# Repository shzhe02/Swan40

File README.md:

# Swan40 - A 40-key split keyboard.

My first attempt at designing a custom sleek split keyboard.

Heavily inspired by the [Corne](https://github.com/foostan/crkbd) and [Ferris Sweep](https://github.com/davidphilipbarr/Sweep).

More extensive write-up (in progress): https://shzhe02.com/projects/swan40

The provided ZMK config is essentially:
- 80% [Corne default zmk config and keymap](https://github.com/zmkfirmware/zmk/tree/main/app/boards/shields/corne)
- 10% [Pnohty config for the Ferris Sweep](https://github.com/rayduck/zmk-config)
- 10% Manual configuration for the Swan40

Features:
- Uses the XIAO nRF528420 microcontroller
- Up to 1000 mAh lipo battery without tenting (with 102050 lipo)
- Dual-orientation lipo mounting
- On-off switch hard wired to battery
- Should be compatible with Choc v1 and v2 switches (only v1 tested)
- Hotswap switches
- Plate-mounted switches

BOM:
- 2x XIAO nRF52840 (compatible with both non-sense or sense versions)
- 2x MSK-12C02 switches
- 40x Kailh Low-profile hotswap sockets
- 40x 1N4148W T4 SOD123 diodes
- Some jumper wires (for connecting the battery pads on the PCB to the battery pads on the microcontroller)
- Electrical tape (place over battery-connected pads on PCB after soldering to reduce chances of a short-circuit occuring)
- 40x Kailh Choc v1/v2 switches
- 40x MBK keycaps (or compatible keycaps of your choice)
- (Optional) 2x MBK homing keycaps (In this case, only 38 normal keycaps are needed)

Optional (but recommended) case: https://www.printables.com/model/561315-swan40-case

Case BOM:
- 3x M2 (OD 3.2mm) x 4mm brass inserts
- 3x M2 x 5mm screws (preferrably button head torx (or hex))
- 2x M2 x 10mm screws

Wiring notes:
- Positive and negative battery terminals should be soldered to the BAT+ and BAT- pads on the PCB respectively.
- The BOARD+ and BOARD- pads on the PCB should be soldered to jumper wires connecting them to the BAT+ and BAT- pads on the microcontroller respectively.
- I recommend first connecting the microcontroller to the PCB and using a multimeter to ensure that the switch works and there are no shorts between the BAT+ and BAT- pads of the PCB before connecting the battery.
- When soldering the battery to the PCB, I recommend doing the following:
  - Tape off the end of one of the battery wires with some sort of insulating tape (I used masking tape).
  - Route the taped wire through the battery wire hole on the PCB (check the write up for more details) followed by the other wire.
  - Solder the non-taped wire to its corresponding battery pad on the PCB.
  - After the pad has cooled down, place some insulating tape over the entire pad but leave the other pad exposed.
  - Un-tape the taped wire and solder it to the other battery pad on the PCB.
  - Remove the tape on the other pad, and cover both pads with electrical tape.

~~Potential future improvements:~~
~~- [ ] Make main PCB reversible~~
~~- [ ] Change lipo connection SMD pads to an SMD micro JST 1.25 connector~~
~~- [ ] Figure out a safer (more foolproof) method to connect battery pads of the controller to the PCB.~~
~~- [ ] Design a smaller battery cover for the 500 mAh 602035 lipo~~

No further hardware development will be done. The keyboard works great for me, but I have a few things I dislike about the board (in no particular order):
1. Bluetooth connections are unreliable, both in the pairing process and during operation. While pairing, this keyboard often just refuses to connect to my computer until I clear all profiles, which is quite annoying. During operation, just playing a phone next to the keyboard adds considerable latency.
2. The shift key is placed too low, which means situations where I must hold the key down for a long time or press it many times are uncomfortable.
3. The cables required to connect the battery to the XIAO board. It requires the case to add otherwise unneccessary height below the PCB for clearance, not to mention that it requires insulation around the contacts to protect agasint battery short circuiting.
4. Dust collects on the non-switch parts of the PCBs.

Any future work will be done on brand new keyboard designs that hopefully address these issues.

Credits:
- [foostan's kbd KiCad Library/Symbols/3D Models](https://github.com/foostan/kbd/tree/crkbd4)
    - Located in the directory: pcb/assets/kbd, plate/assets/kbd, left-plate/assets/kbd, and right-plate/assets/kbd
- [Seeed Studio XIAO nRF52840 STEP model - by Maurice Pannard](https://grabcad.com/library/seeed-studio-xiao-nrf52840-sense-1)
    - Located in the directory: pcb/assets/xiao_nrf52840
- [Kailh 1350 Socket (Choc V1 Hotswap sockets) STEP model - by Dennis Lee](https://grabcad.com/library/kailh-1350-socket-2)
    - Located in the directory: pcb/assets/kailh_choc_v1_hotswap
- [MBK Choc Low Profile 1u keycap STEP model - by darryldh](https://www.thingiverse.com/thing:4564253)
    - Located in the directory: pcb/assets/kailh_choc_v1_hotswap
- [MSK-12C02 SMD Slider Switch Footprint - by mzst](https://mzstblog.blogspot.com/2016/01/msk-12c02-smd-slider-switch-spdt-eagle.html)
    - Located in the directory: pcb/assets/MSK-12C02
- Rayduck and Foostan for the ZMK config

Note: Modifications were made to many of the assets.

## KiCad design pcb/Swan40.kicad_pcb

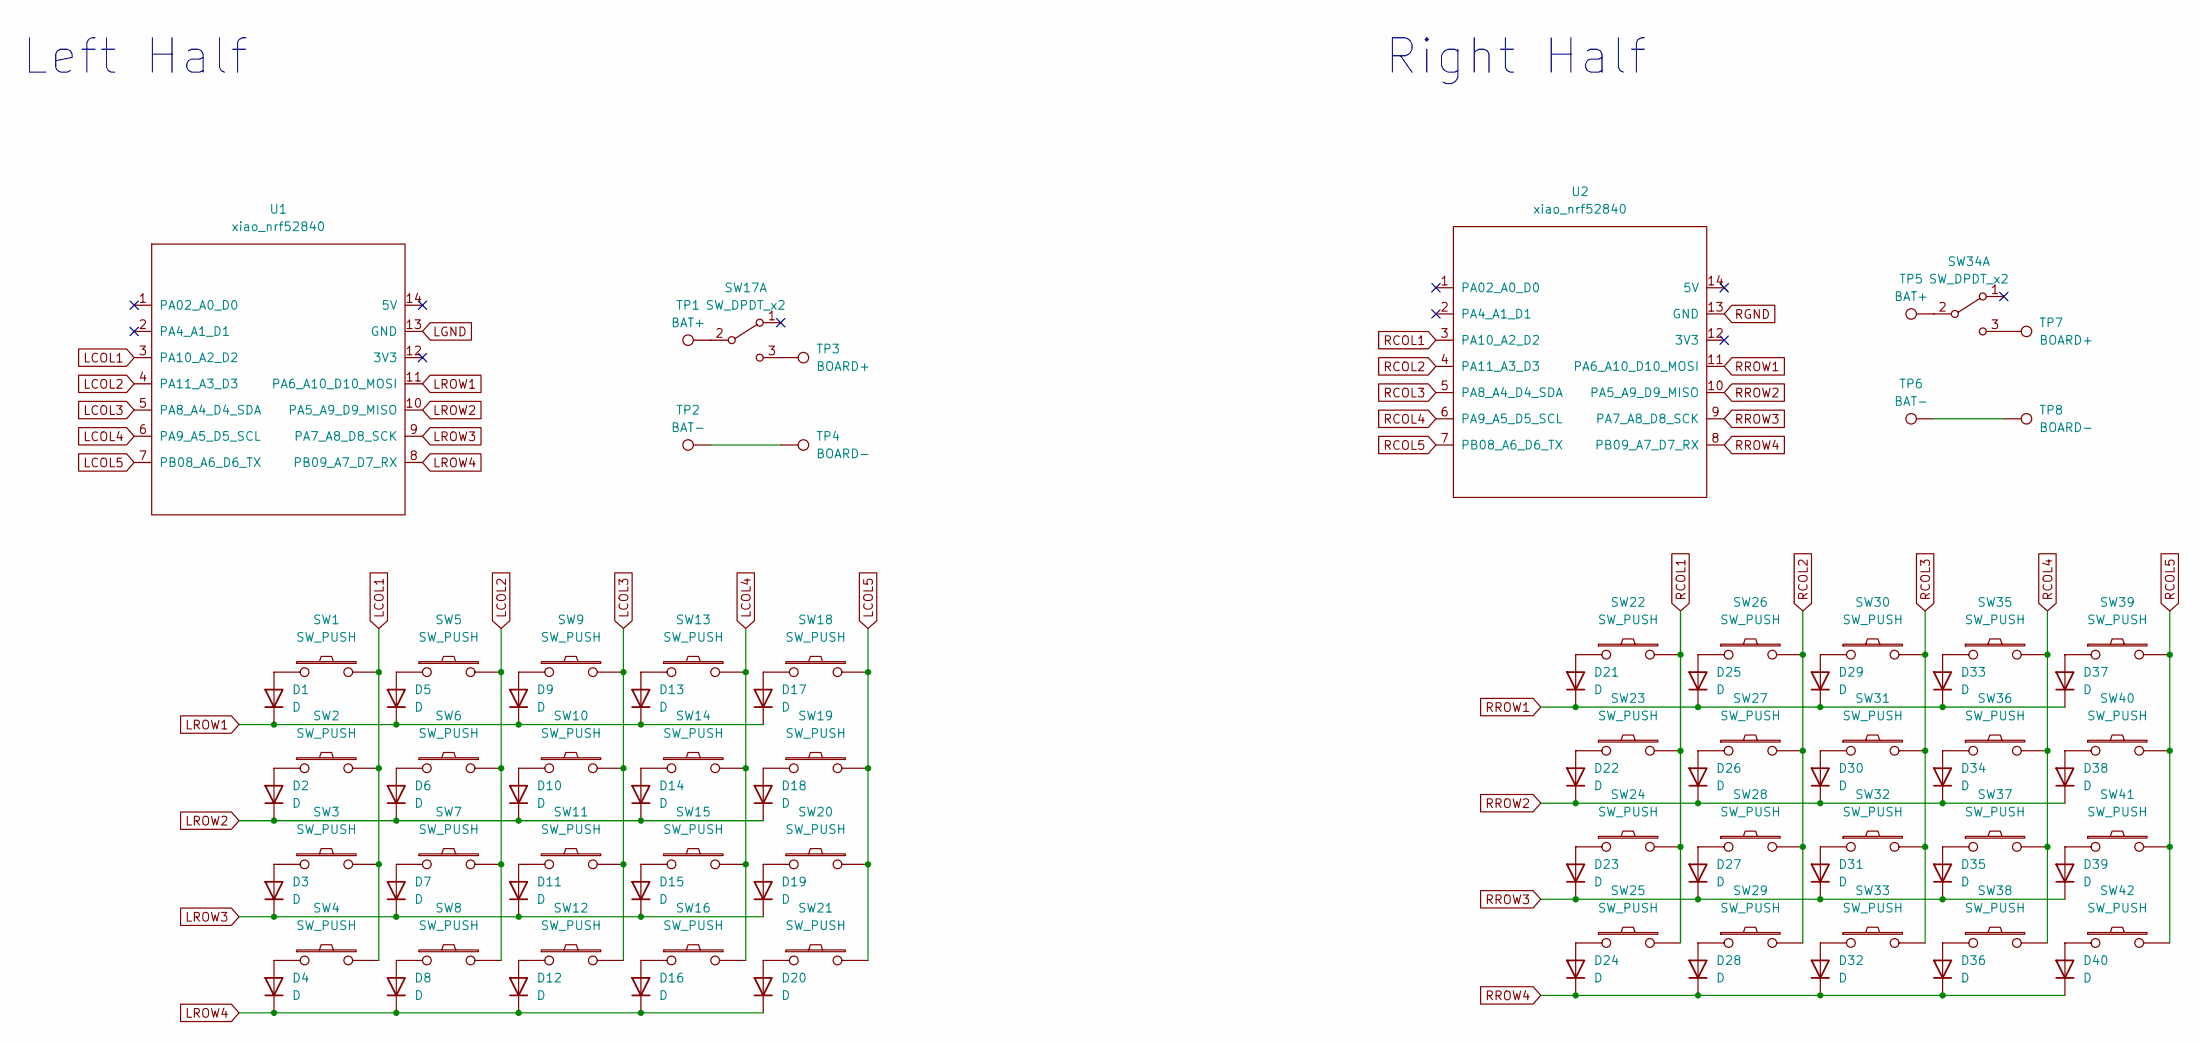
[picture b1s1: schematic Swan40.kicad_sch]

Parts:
D1, D2, D3, D4, D5, D6, D7, D8, D9, D10, D11, D12, D13, D14, D15, D16, D17, D18, D19, D20, D21, D22, D23, D24, D25, D26, D27, D28, D29, D30, D31, D32, D33, D34, D35, D36, D37, D38, D39, D40: D; D3_SMD_v2
SW1, SW2, SW3, SW4, SW5, SW6, SW7, SW8, SW9, SW10, SW11, SW12, SW13, SW14, SW15, SW16, SW18, SW19, SW20, SW21, SW22, SW23, SW24, SW25, SW26, SW27, SW28, SW29, SW30, SW31, SW32, SW33, SW35, SW36, SW37, SW38, SW39, SW40, SW41, SW42: SW_PUSH; ChocV1_V2_Hotswap
SW17, SW34: SW_DPDT_x2; MSK-12C02
TP1, TP5: BAT+; 1pad_conn_board
TP2, TP6: BAT-; 1pad_conn_board
TP3, TP7: BOARD+; 1pad_conn_board
TP4, TP8: BOARD-; 1pad_conn_board
U1, U2: xiao_nrf52840; xiao_nrf52840_v2

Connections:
LCOL1: SW1.2, SW2.2, SW3.2, SW4.2, U1.3 (PA10_A2_D2)
LCOL2: SW5.2, SW6.2, SW7.2, SW8.2, U1.4 (PA11_A3_D3)
LCOL3: SW9.2, SW10.2, SW11.2, SW12.2, U1.5 (PA8_A4_D4_SDA)
LCOL4: SW13.2, SW14.2, SW15.2, SW16.2, U1.6 (PA9_A5_D5_SCL)
LCOL5: SW18.2, SW19.2, SW20.2, SW21.2, U1.7 (PB08_A6_D6_TX)
LGND: U1.13 (GND)
LROW1: D1.1 (K), D5.1 (K), D9.1 (K), D13.1 (K), D17.1 (K), U1.11 (PA6_A10_D10_MOSI)
LROW2: D2.1 (K), D6.1 (K), D10.1 (K), D14.1 (K), D18.1 (K), U1.10 (PA5_A9_D9_MISO)
LROW3: D3.1 (K), D7.1 (K), D11.1 (K), D15.1 (K), D19.1 (K), U1.9 (PA7_A8_D8_SCK)
LROW4: D4.1 (K), D8.1 (K), D12.1 (K), D16.1 (K), D20.1 (K), U1.8 (PB09_A7_D7_RX)
unnamed: D1.2 (A), SW1.1
unnamed: D2.2 (A), SW2.1
unnamed: D3.2 (A), SW3.1
unnamed: D4.2 (A), SW4.1
unnamed: D5.2 (A), SW5.1
unnamed: D6.2 (A), SW6.1
unnamed: D7.2 (A), SW7.1
unnamed: D8.2 (A), SW8.1
unnamed: D9.2 (A), SW9.1
unnamed: D10.2 (A), SW10.1
unnamed: D11.2 (A), SW11.1
unnamed: D12.2 (A), SW12.1
unnamed: D13.2 (A), SW13.1
unnamed: D14.2 (A), SW14.1
unnamed: D15.2 (A), SW15.1
unnamed: D16.2 (A), SW16.1
unnamed: D17.2 (A), SW18.1
unnamed: D18.2 (A), SW19.1
unnamed: D19.2 (A), SW20.1
unnamed: D20.2 (A), SW21.1
unnamed: D21.2 (A), SW22.1
unnamed: D22.2 (A), SW23.1
unnamed: D23.2 (A), SW24.1
unnamed: D24.2 (A), SW25.1
unnamed: D25.2 (A), SW26.1
unnamed: D26.2 (A), SW27.1
unnamed: D27.2 (A), SW28.1
unnamed: D28.2 (A), SW29.1
unnamed: D29.2 (A), SW30.1
unnamed: D30.2 (A), SW31.1
unnamed: D31.2 (A), SW32.1
unnamed: D32.2 (A), SW33.1
unnamed: D33.2 (A), SW35.1
unnamed: D34.2 (A), SW36.1
unnamed: D35.2 (A), SW37.1
unnamed: D36.2 (A), SW38.1
unnamed: D37.2 (A), SW39.1
unnamed: D38.2 (A), SW40.1
unnamed: D39.2 (A), SW41.1
unnamed: D40.2 (A), SW42.1
unnamed 50: SW17.2 (B), TP1.1; also elsewhere on the board
unnamed 51: SW17.3 (C), TP3.1; also elsewhere on the board
unnamed 52: SW34.2 (B), TP5.1; also elsewhere on the board
unnamed 53: SW34.3 (C), TP7.1; also elsewhere on the board
unnamed 54: TP2.1, TP4.1; also elsewhere on the board
unnamed 55: TP6.1, TP8.1; also elsewhere on the board
RCOL1: SW22.2, SW23.2, SW24.2, SW25.2, U2.3 (PA10_A2_D2)
RCOL2: SW26.2, SW27.2, SW28.2, SW29.2, U2.4 (PA11_A3_D3)
RCOL3: SW30.2, SW31.2, SW32.2, SW33.2, U2.5 (PA8_A4_D4_SDA)
RCOL4: SW35.2, SW36.2, SW37.2, SW38.2, U2.6 (PA9_A5_D5_SCL)
RCOL5: SW39.2, SW40.2, SW41.2, SW42.2, U2.7 (PB08_A6_D6_TX)
RGND: U2.13 (GND)
RROW1: D21.1 (K), D25.1 (K), D29.1 (K), D33.1 (K), D37.1 (K), U2.11 (PA6_A10_D10_MOSI)
RROW2: D22.1 (K), D26.1 (K), D30.1 (K), D34.1 (K), D38.1 (K), U2.10 (PA5_A9_D9_MISO)
RROW3: D23.1 (K), D27.1 (K), D31.1 (K), D35.1 (K), D39.1 (K), U2.9 (PA7_A8_D8_SCK)
RROW4: D24.1 (K), D28.1 (K), D32.1 (K), D36.1 (K), D40.1 (K), U2.8 (PB09_A7_D7_RX)

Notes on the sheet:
Right Half
Left Half

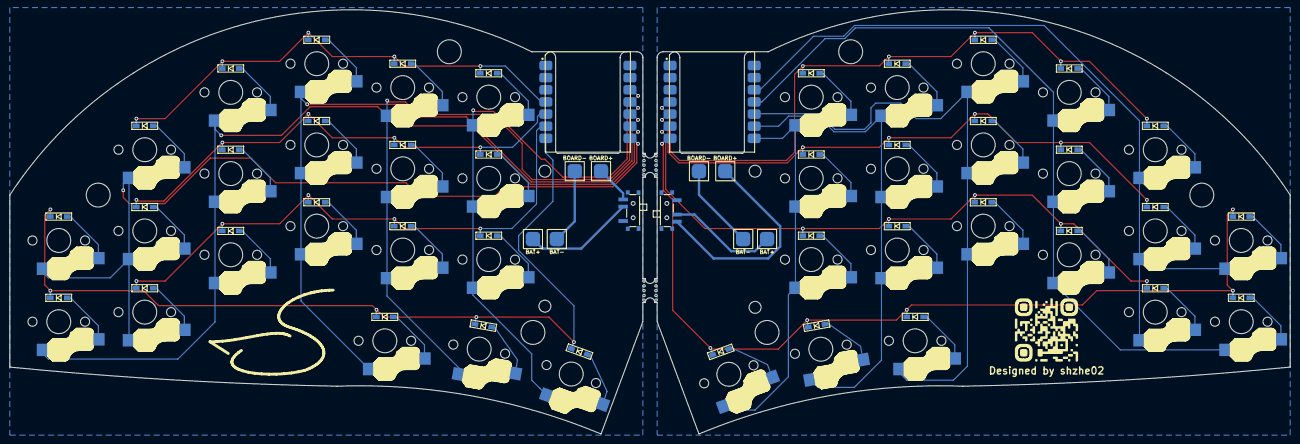
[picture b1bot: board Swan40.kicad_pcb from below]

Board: 2 copper layers, 268.0 x 88.8 mm, 92 parts (52 on the bottom side), 64 nets.

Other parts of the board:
BAT+: BAT+; 1pad_conn_board
BAT+#2: BAT+; 1pad_conn_board
BAT-: BAT-; 1pad_conn_board
BAT-#2: BAT-; 1pad_conn_board
BOARD+: BOARD+; 1pad_conn_board
BOARD+#2: BOARD+; 1pad_conn_board
BOARD-: BOARD-; 1pad_conn_board
BOARD-#2: BOARD-; 1pad_conn_board

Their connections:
unnamed 50: BAT+#2.1; also elsewhere on the board
unnamed 51: BOARD+.1; also elsewhere on the board
unnamed 52: BAT+.1; also elsewhere on the board
unnamed 53: BOARD+#2.1; also elsewhere on the board
unnamed 54: BAT-#2.1, BOARD-.1; also elsewhere on the board
unnamed 55: BAT-.1, BOARD-#2.1; also elsewhere on the board

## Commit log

2023-08-05 Semi-broken 1st attempt
2023-08-06 Base wiring completed
2023-08-06 Updated board outline
2023-08-08 Wiring complete
2023-08-08 Fixed errors + Rounded tracks
2023-08-09 Rounded + added droplets + fill zones
2023-08-10 Added base kibot automation
2023-08-10 Fixed workflow
2023-08-10 Attempted fix
2023-08-10 Switched to rounded file
2023-08-10 Fixed typo
2023-08-10 Runs action every time
2023-08-11 Everything re-aligned and re-wired
2023-08-11 Updated violations
2023-08-11 Added mouse bites
2023-08-11 Fixed schematic warnings
2023-08-11 Fixed JLCPCB config
2023-08-11 Removed everything from JLCPCB config besides gerber and drill files
2023-08-11 Designed + Export automation (#1)
    * Base wiring completed
    * Updated board outline
    * Wiring complete
    * Fixed errors + Rounded tracks
    * Rounded + added droplets + fill zones
    * Added base kibot automation
2023-08-12 Refactored folders, added plates
2023-08-12 Fixed typo in workflows
2023-08-12 Fixed config import
2023-08-12 Combined all workflows
2023-08-12 Renamed jobs
2023-08-12 Added reversable plate
2023-08-12 Editted footprint
2023-08-12 Updated unrounded PCB with silkscreens + updated workflow
2023-08-12 Refactored + Polished (#2)
    * Refactored folders, added plates
    * Fixed typo in workflows
    * Fixed config import
    * Combined all workflows
    * Renamed jobs
    * Added reversable plate
2023-08-23 added documentation
2023-08-23 Modified README
2023-08-23 Added config, updated README
2023-08-23 Updated workflow
2023-08-23 Fixing zmk config
2023-08-30 Attempted fix for sleep
2023-09-11 Create LICENSE
